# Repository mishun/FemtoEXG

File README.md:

FemtoEXG
========

A simple small-sized DIY bioamplifier + ADC module that can be used
(hopefully) for EEG, ECG or EMG. Made in Eagle CAD.

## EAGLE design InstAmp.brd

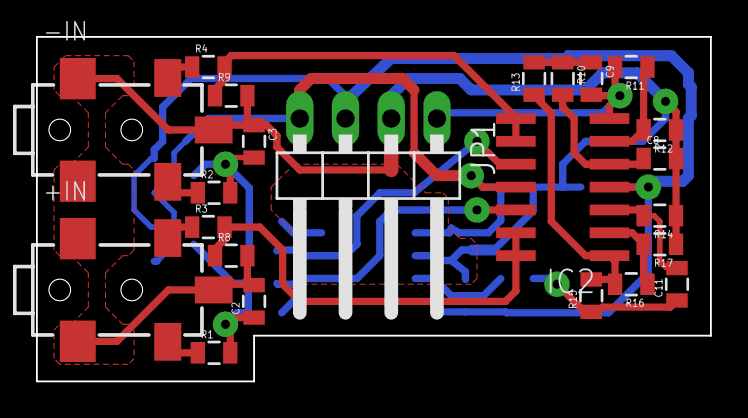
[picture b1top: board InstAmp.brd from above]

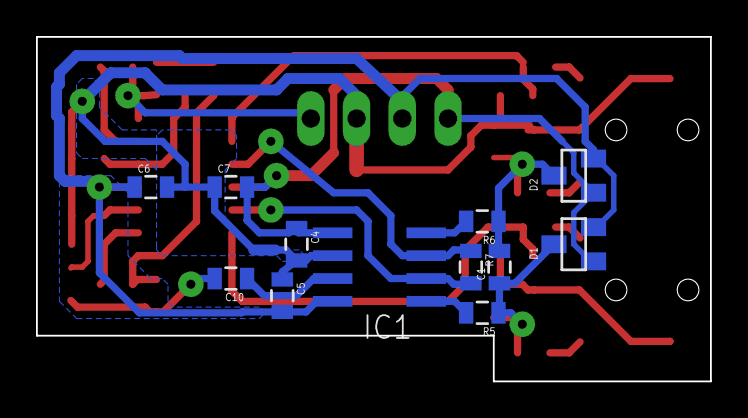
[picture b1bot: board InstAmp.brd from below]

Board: 2 copper layers, 37.4 x 19.1 mm, 35 parts (12 on the bottom side), 24 nets.

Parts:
+IN: AUDIOJACK2.5-SMD
-IN: AUDIOJACK2.5-SMD
C1: 10pF; 0805
C2, C3: 100pF; 0805
C4, C5, C6, C7: 100nF; 0805
C8: 47nF; 0805
C9: 33nF; 0805
C10, C11: 1uF; 0805
D1, D2: BAV199; SOT23
IC1: AD8221ARZ
IC2: TLC2254ID; SO14
JP1: OUT; 1X04/90
R1, R2, R5, R6: 2k2; 0805
R3, R4: 100; 0805
R7: 2k; 0805
R8, R9, R10, R11, R12, R13, R14, R17: 100k; 0805
R15: 680k; 0805
R16: 910k; 0805

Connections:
+5V: C5.2, C6.1, D1.2, D2.2, IC1.8, IC2.4, JP1.3
-5V: C4.1, C7.2, D1.1, D2.1, IC1.5, IC2.11, JP1.4
GND: +IN.GND1, +IN.GND2, +IN.SW, -IN.GND1, -IN.GND2, -IN.SW, C2.2, C3.1, C4.2, C5.1, C6.2, C7.1, C8.2, IC1.6, JP1.2, R8.2, R9.2, R12.1, R14.1, R17.1
unnamed: +IN.L, R1.1
unnamed: -IN.R, R4.1
unnamed: +IN.R, R3.1
unnamed: -IN.L, R2.1
unnamed: C1.2, C3.2, D2.3, R2.2, R6.1
unnamed: C1.1, C2.1, D1.3, R1.2, R5.1
unnamed: IC2.8, IC2.9, R4.2, R9.1
unnamed: IC1.3, IC2.10, R7.1
unnamed: IC2.1, R13.1, R15.2, R16.2
unnamed: IC2.2, R16.1, R17.2
unnamed: C10.1, IC1.7
unnamed: IC1.1, R5.2
unnamed: IC1.4, R6.2
unnamed: C8.1, IC2.5, R10.2
unnamed: C9.1, R10.1, R13.2
unnamed: IC1.2, IC2.12, R7.2
unnamed: IC2.13, IC2.14, R3.2, R8.1
unnamed: C10.2, C11.1, R15.1
unnamed: C11.2, IC2.3, R14.2
unnamed: IC2.6, R11.1, R12.2
OUT: C9.2, IC2.7, JP1.1, R11.2

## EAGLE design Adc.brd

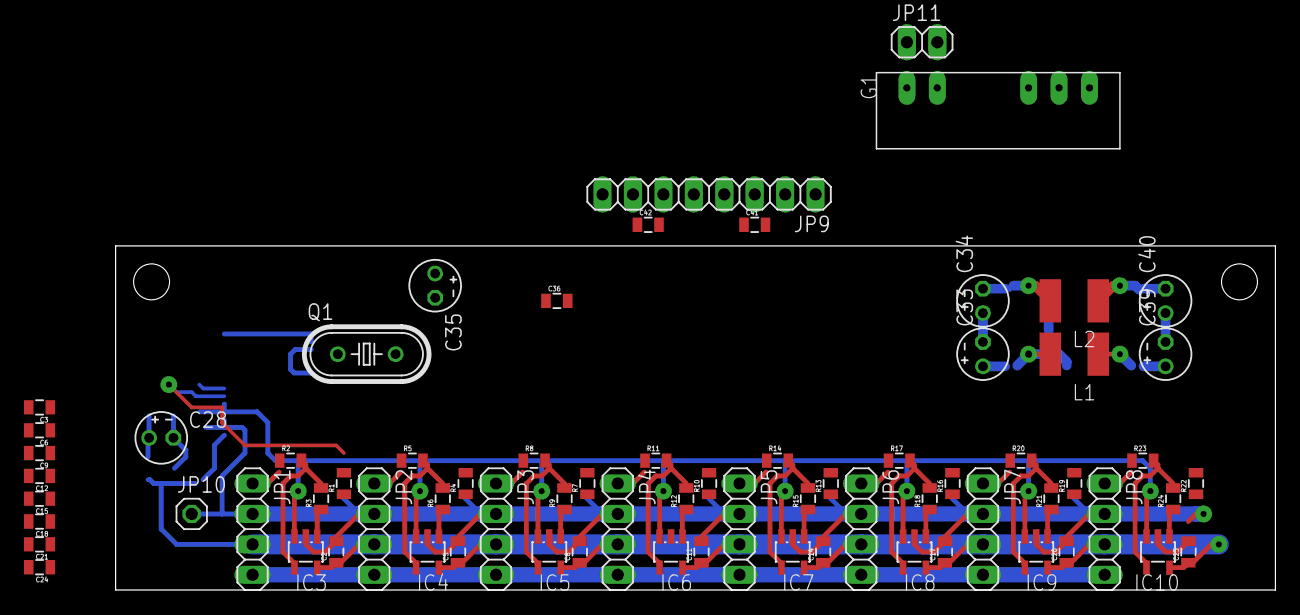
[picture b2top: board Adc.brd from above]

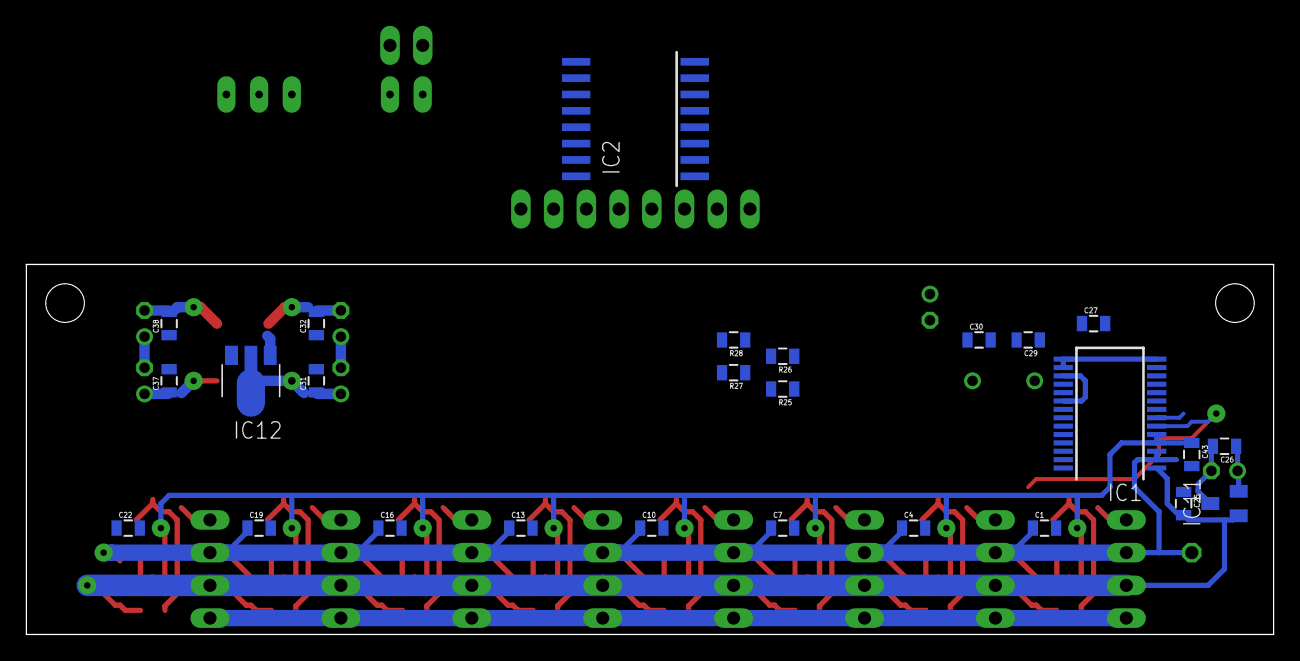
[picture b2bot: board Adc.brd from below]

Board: 2 copper layers, 96.8 x 28.7 mm, 98 parts (26 on the bottom side), 57 nets.

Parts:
C1, C2, C3, C4, C5, C6, C7, C8, C9, C10, C11, C12, C13, C14, C15, C16, C17, C18, C19, C20, C21, C22, C23, C24, C25, C26, C27, C31, C32, C36, C37, C38, C41, C42: 100nF; 0805
C28, C33, C34, C35, C39, C40: 47uF; E2-4
C29, C30: 18pF; 0805
C43: 100pF; 0805
G1: TMV0505D
IC1: ADS1256IDBT
IC2: ADUM1402ARWZ
IC3, IC4, IC5, IC6, IC7, IC8, IC9, IC10: AD8605ARTZ
IC11: REF3125AIDBZT
IC12: MCP170333MB; SOT89
JP1, JP2, JP3, JP4, JP5, JP6, JP7, JP8: 1X04
JP9: 1X08
JP10: 1X01
JP11: 1X02
L1, L2: L4532P
Q1: 7.68MHz; HC49U-V
R1, R4, R7, R10, R13, R16, R19, R22, R25, R26, R27, R28: 100; 0805
R2, R3, R5, R6, R8, R9, R11, R12, R14, R15, R17, R18, R20, R21, R23, R24: 1k; 0805

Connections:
+3.3V: C27.1, C35.+, C36.1, C41.2, IC1.14, IC1.15, IC1.16, IC2.1, IC2.7, IC12.3
+5VA: C2.1, C5.1, C8.1, C11.1, C14.1, C17.1, C20.1, C23.1, C25.2, C37.1, C39.+, IC1.1, IC3.5, IC4.5, IC5.5, IC6.5, IC7.5, IC8.5, IC9.5, IC10.5, IC11.1, JP1.3, JP2.3, JP3.3, JP4.3, JP5.3, JP6.3, JP7.3, JP8.3, L1.1
-5VA: C38.2, C40.-, JP1.4, JP2.4, JP3.4, JP4.4, JP5.4, JP6.4, JP7.4, JP8.4, L2.1
GND: C1.1, C2.2, C3.2, C4.1, C5.2, C6.2, C7.1, C8.2, C9.2, C10.1, C11.2, C12.2, C13.1, C14.2, C15.2, C16.1, C17.2, C18.2, C19.1, C20.2, C21.2, C22.1, C23.2, C24.2, C25.1, C26.2, C27.2, C28.-, C29.2, C30.2, C31.2, C32.1, C33.-, C34.+, C35.-, C36.2, C37.2, C38.1, C39.-, C40.+, C41.1, C43.2, G1.6, IC1.2, IC1.3, IC1.17, IC1.20, IC2.2, IC2.8, IC3.2, IC4.2, IC5.2, IC6.2, IC7.2, IC8.2, IC9.2, IC10.2, IC11.3, IC12.1, JP1.2, JP2.2, JP3.2, JP4.2, JP5.2, JP6.2, JP7.2, JP8.2, JP10.1
unnamed: IC3.4, R2.2, R3.2
unnamed: IC3.1, R1.1, R3.1
unnamed: JP1.1, R2.1
unnamed: C3.1, IC1.6, R1.2
unnamed: IC4.4, R5.2, R6.2
unnamed: IC4.1, R4.1, R6.1
unnamed: C6.1, IC1.7, R4.2
unnamed: JP2.1, R5.1
unnamed: IC5.4, R8.2, R9.2
unnamed: IC5.1, R7.1, R9.1
unnamed: C9.1, IC1.8, R7.2
unnamed: JP3.1, R8.1
unnamed: IC6.4, R11.2, R12.2
unnamed: IC6.1, R10.1, R12.1
unnamed: C12.1, IC1.9, R10.2
unnamed: JP4.1, R11.1
unnamed: IC7.4, R14.2, R15.2
unnamed: IC7.1, R13.1, R15.1
unnamed: C15.1, IC1.10, R13.2
unnamed: JP5.1, R14.1
unnamed: IC8.4, R17.2, R18.2
unnamed: IC8.1, R16.1, R18.1
unnamed: C18.1, IC1.11, R16.2
unnamed: JP6.1, R17.1
unnamed: IC9.4, R20.2, R21.2
unnamed: IC9.1, R19.1, R21.1
unnamed: C21.1, IC1.12, R19.2
unnamed: JP7.1, R20.1
unnamed: IC10.4, R23.2, R24.2
unnamed: IC10.1, R22.1, R24.1
unnamed: C24.1, IC1.13, R22.2
unnamed: JP8.1, R23.1
unnamed: C29.1, IC1.18, Q1.1
unnamed: C30.1, IC1.19, Q1.2
unnamed: IC2.11, JP9.7
unnamed: IC1.21, R25.1
unnamed: IC1.24, R26.1
unnamed: IC1.23, R27.1
unnamed: IC1.22, R28.1
unnamed: C42.1, IC2.9, IC2.15, JP9.8
unnamed: C31.1, C33.+, G1.7, IC12.2@1, L1.2
unnamed: C32.2, C34.-, G1.5, L2.2
unnamed: C42.2, IC2.10, IC2.16, JP9.3
unnamed: IC2.3, R25.2
unnamed: IC2.4, R28.2
unnamed: IC2.5, R26.2
unnamed: IC2.6, R27.2
unnamed: IC2.12, JP9.6
unnamed: IC2.13, JP9.5
unnamed: IC2.14, JP9.4
unnamed: G1.1, JP11.1
unnamed: G1.2, JP11.2
REF: C1.2, C4.2, C7.2, C10.2, C13.2, C16.2, C19.2, C22.2, C26.1, C28.+, C43.1, IC1.4, IC1.5, IC3.3, IC4.3, IC5.3, IC6.3, IC7.3, IC8.3, IC9.3, IC10.3, IC11.2

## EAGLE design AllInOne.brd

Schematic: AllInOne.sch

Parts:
C1, C30, C45, C61, C75, C89, C103, C117: 10pF; C0805
C2, C3, C31, C32, C46, C47, C62, C63, C76, C77, C90, C91, C104, C105, C118, C119: 100pF; C0805
C4, C5, C6, C7, C8, C11, C15, C16, C17, C18, C19, C24, C25, C26, C28, C33, C34, C35, C36, C39, C40, C43, C44, C48, C49, C50, C51, C52, C55, C57, C60, C64, C65, C66, C67, C70, C71, C74, C78, C79, C80, C81, C84, C85, C88, C92, C93, C94, C95, C98, C99, C102, C106, C107, C108, C109, C112, C113, C116, C120, C121, C122, C123, C126, C127, C130: 0.1; C0805
C9, C10: 18p; C0805
C12, C13, C37, C38, C53, C54, C68, C69, C82, C83, C96, C97, C110, C111, C124, C125: 1u; C0805
C14, C41, C58, C72, C86, C100, C114, C128: 47n; C0805
C20, C21, C22, C23, C27, C29: 47u; E2-4
C42, C56, C59, C73, C87, C101, C115, C129: 33n; C0805
COM: COM; 1X02
D1, D2, D3, D4, D5, D6, D7, D8, D9, D10, D11, D12, D13, D14, D15, D16, D17, D18, D19, D20, D21, D22, D23, D24, D25, D26, D27, D28, D29, D30, D31, D32: BAV199; SOT23
G1: TMV0505D
IC1, IC8, IC11, IC14, IC17, IC20, IC23, IC26: AD8221ARZ; SO-08
IC2, IC9, IC12, IC15, IC18, IC21, IC24, IC27: TLC2254ID
IC3: ADS1256IDBT
IC4, IC10, IC13, IC16, IC19, IC22, IC25, IC28: AD8605ARTZ
IC5: MCP170333MB; SOT89
IC6: ADUM1402ARWZ
IC7: REF3125AIDBZT
IN1: IN1; 1X04
IN2: IN2; 1X04
IN3: IN3; 1X04
IN4: IN4; 1X04
IN5: IN5; 1X04
IN6: IN6; 1X04
IN7: IN7; 1X04
IN8: IN8; 1X04
INT: INT; 1X08
L1, L2: 100uH; L4532P
Q1: 8MHz; HC49U-V
R1, R2, R5, R6, R24, R26, R29, R30, R45, R46, R49, R50, R65, R66, R69, R70, R85, R86, R89, R90, R105, R106, R109, R110, R125, R126, R129, R130, R145, R146, R149, R150: 2K2; R0805
R3, R4, R14, R15, R16, R17, R18, R27, R28, R44, R47, R48, R64, R67, R68, R84, R87, R88, R104, R107, R108, R124, R127, R128, R144, R147, R148, R164: 100; R0805
R7, R31, R51, R71, R91, R111, R131, R151: 2K; R0805
R8, R9, R10, R13, R19, R20, R21, R23, R32, R33, R34, R37, R38, R41, R42, R43, R52, R53, R54, R57, R58, R61, R62, R63, R72, R73, R74, R77, R78, R81, R82, R83, R92, R93, R94, R97, R98, R101, R102, R103, R112, R113, R114, R117, R118, R121, R122, R123, R132, R133, R134, R137, R138, R141, R142, R143, R152, R153, R154, R157, R158, R161, R162, R163: 100K; R0805
R11, R35, R55, R75, R95, R115, R135, R155: 910K; R0805
R12, R36, R56, R76, R96, R116, R136, R156: 680K; R0805
R22, R25, R39, R40, R59, R60, R79, R80, R99, R100, R119, R120, R139, R140, R159, R160: 1K; R0805

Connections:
+3.3V: C7.1, C17.1, C21.+, C44.1, IC3.14 (SYNC/PDWN), IC3.15 (RESET), IC3.16 (DVDD), IC5.3 (VO), IC6.1 (VDD1), IC6.7 (VE1)
+5VA: C5.2, C6.1, C8.1, C15.1, C26.1, C27.+, C34.2, C35.1, C39.1, C49.2, C50.1, C55.1, C65.2, C66.1, C70.1, C79.2, C80.1, C84.1, C93.2, C94.1, C98.1, C107.2, C108.1, C112.1, C121.2, C122.1, C126.1, D1.2 (C), D2.2 (C), D3.2 (C), D4.2 (C), D5.2 (C), D6.2 (C), D7.2 (C), D8.2 (C), D9.2 (C), D10.2 (C), D11.2 (C), D12.2 (C), D13.2 (C), D14.2 (C), D15.2 (C), D16.2 (C), D17.2 (C), D18.2 (C), D19.2 (C), D20.2 (C), D21.2 (C), D22.2 (C), D23.2 (C), D24.2 (C), D25.2 (C), D26.2 (C), D27.2 (C), D28.2 (C), D29.2 (C), D30.2 (C), D31.2 (C), D32.2 (C), IC1.8 (+VS), IC2.4 (+VS), IC3.1 (AVDD), IC4.5 (+VS), IC7.1 (VIN), IC8.8 (+VS), IC9.4 (+VS), IC10.5 (+VS), IC11.8 (+VS), IC12.4 (+VS), IC13.5 (+VS), IC14.8 (+VS), IC15.4 (+VS), IC16.5 (+VS), IC17.8 (+VS), IC18.4 (+VS), IC19.5 (+VS), IC20.8 (+VS), IC21.4 (+VS), IC22.5 (+VS), IC23.8 (+VS), IC24.4 (+VS), IC25.5 (+VS), IC26.8 (+VS), IC27.4 (+VS), IC28.5 (+VS), L1.1
-5VA: C4.1, C11.2, C28.2, C29.-, C33.1, C36.2, C48.1, C51.2, C64.1, C67.2, C78.1, C81.2, C92.1, C95.2, C106.1, C109.2, C120.1, C123.2, D1.1 (A), D2.1 (A), D3.1 (A), D4.1 (A), D5.1 (A), D6.1 (A), D7.1 (A), D8.1 (A), D9.1 (A), D10.1 (A), D11.1 (A), D12.1 (A), D13.1 (A), D14.1 (A), D15.1 (A), D16.1 (A), D17.1 (A), D18.1 (A), D19.1 (A), D20.1 (A), D21.1 (A), D22.1 (A), D23.1 (A), D24.1 (A), D25.1 (A), D26.1 (A), D27.1 (A), D28.1 (A), D29.1 (A), D30.1 (A), D31.1 (A), D32.1 (A), IC1.5 (-VS), IC2.11 (-VS), IC8.5 (-VS), IC9.11 (-VS), IC11.5 (-VS), IC12.11 (-VS), IC14.5 (-VS), IC15.11 (-VS), IC17.5 (-VS), IC18.11 (-VS), IC20.5 (-VS), IC21.11 (-VS), IC23.5 (-VS), IC24.11 (-VS), IC26.5 (-VS), IC27.11 (-VS), L2.1
CH1SW1: IC2.7 (OUT2), R11.1, R12.2, R20.2
CH1SW2: IC9.7 (OUT2), R35.1, R36.2, R38.2
CH1SW3: IC12.7 (OUT2), R55.1, R56.2, R58.2
CH1SW4: IC15.7 (OUT2), R75.1, R76.2, R78.2
CH1SW5: IC18.7 (OUT2), R95.1, R96.2, R98.2
CH1SW6: IC21.7 (OUT2), R115.1, R116.2, R118.2
CH1SW7: IC24.7 (OUT2), R135.1, R136.2, R138.2
CH1SW8: IC27.7 (OUT2), R155.1, R156.2, R158.2
GND: C2.2, C3.1, C4.2, C5.1, C6.2, C7.2, C8.2, C9.2, C10.2, C11.1, C14.2, C15.2, C16.2, C17.2, C19.1, C20.-, C21.-, C22.-, C23.+, C24.2, C25.1, C26.2, C27.-, C28.1, C29.+, C31.2, C32.1, C33.2, C34.1, C35.2, C36.1, C39.2, C40.1, C41.2, C43.1, C44.2, C46.2, C47.1, C48.2, C49.1, C50.2, C51.1, C52.1, C55.2, C57.1, C58.2, C60.1, C62.2, C63.1, C64.2, C65.1, C66.2, C67.1, C70.2, C71.1, C72.2, C74.1, C76.2, C77.1, C78.2, C79.1, C80.2, C81.1, C84.2, C85.1, C86.2, C88.1, C90.2, C91.1, C92.2, C93.1, C94.2, C95.1, C98.2, C99.1, C100.2, C102.1, C104.2, C105.1, C106.2, C107.1, C108.2, C109.1, C112.2, C113.1, C114.2, C116.1, C118.2, C119.1, C120.2, C121.1, C122.2, C123.1, C126.2, C127.1, C128.2, C130.1, COM.1, COM.2, G1.6 (COM), IC1.6 (REF), IC3.2 (AGND), IC3.3 (VREFN), IC3.17 (DGND), IC3.20 (CS), IC4.2 (-VS), IC5.1 (GND), IC6.2 (GND1), IC6.8 (GND1_), IC7.3 (GND), IC8.6 (REF), IC10.2 (-VS), IC11.6 (REF), IC13.2 (-VS), IC14.6 (REF), IC16.2 (-VS), IC17.6 (REF), IC19.2 (-VS), IC20.6 (REF), IC22.2 (-VS), IC23.6 (REF), IC25.2 (-VS), IC26.6 (REF), IC28.2 (-VS), R8.2, R9.2, R10.1, R13.2, R21.2, R32.2, R33.2, R34.1, R37.2, R42.2, R52.2, R53.2, R54.1, R57.2, R62.2, R72.2, R73.2, R74.1, R77.2, R82.2, R92.2, R93.2, R94.1, R97.2, R102.2, R112.2, R113.2, R114.1, R117.2, R122.2, R132.2, R133.2, R134.1, R137.2, R142.2, R152.2, R153.2, R154.1, R157.2, R162.2
unnamed: IN1.3, R3.1
unnamed: IN1.2, R4.1
unnamed: IN1.4, R1.1
unnamed: IN1.1, R2.1
unnamed: IC1.1 (-IN), R5.2
unnamed: IC1.4 (+IN), R6.2
unnamed: C1.1, C2.1, D1.3 (AC), R1.2, R5.1
unnamed: C1.2, C3.2, D2.3 (AC), R2.2, R6.1
unnamed: IC1.2 (-RG), IC2.10 (+IN3), R7.2
unnamed: IC1.3 (+RG), IC2.12 (+IN4), R7.1
unnamed: IC3.21 (DRDY), R14.1
unnamed: C10.1, IC3.18 (XTAL2), Q1.1
unnamed: C9.1, IC3.19 (XTAL1/CLKIN), Q1.2
unnamed: IC3.24 (SCLK), R15.1
unnamed: C13.2, IC2.5 (+IN2), R13.1
unnamed: IC2.6 (-IN2), R10.2, R11.2
unnamed: C12.2, C13.1, R12.1
unnamed: C12.1, IC1.7 (OUT)
unnamed: IC2.2 (-IN1), R21.1, R23.1
unnamed: C14.1, IC2.3 (+IN1), R19.1
unnamed: IC4.1 (OUT), R18.2, R25.2
unnamed: IC3.23 (DIN), R16.1
unnamed: IC3.22 (DOUT), R17.1
unnamed: D4.3 (AC), IC2.13 (-IN4), IC2.14 (OUT4), R4.2, R9.1
unnamed: D3.3 (AC), IC2.8 (OUT3), IC2.9 (-IN3), R3.2, R8.1
unnamed: C19.2, IC3.6 (AIN0), R18.1
unnamed: C56.1, R19.2, R20.1
unnamed: IC4.4 (-IN), R22.1, R25.1
unnamed: IN2.3, R27.1
unnamed: IC6.3 (VIA), R14.2
unnamed: IC6.4 (VIB), R17.2
unnamed: IC6.5 (VOC), R15.2
unnamed: IC6.6 (VOD), R16.2
unnamed: G1.1 (+VIN), INT.1
unnamed: C18.2, IC6.9 (GND2_), IC6.15 (GND2), INT.8
unnamed: C18.1, IC6.10 (VE2), IC6.16 (VDD2), INT.3
unnamed: C22.+, C24.1, G1.7 (+VOUT), IC5.2@1 (VI1), L1.2
unnamed: IC6.11 (VID), INT.7
unnamed: IC6.12 (VIC), INT.6
unnamed: IC6.13 (VOB), INT.5
unnamed: IC6.14 (VOA), INT.4
unnamed: C23.-, C25.2, G1.5 (-VOUT), L2.2
unnamed: IN2.2, R28.1
unnamed: IN2.4, R24.1
unnamed: IN2.1, R26.1
unnamed: IC8.1 (-IN), R29.2
unnamed: C30.1, C31.1, D5.3 (AC), R24.2, R29.1
unnamed: C30.2, C32.2, D6.3 (AC), R26.2, R30.1
unnamed: IC8.2 (-RG), IC9.10 (+IN3), R31.2
unnamed: IC8.3 (+RG), IC9.12 (+IN4), R31.1
unnamed: IC8.4 (+IN), R30.2
unnamed: D8.3 (AC), IC9.13 (-IN4), IC9.14 (OUT4), R28.2, R33.1
unnamed: D7.3 (AC), IC9.8 (OUT3), IC9.9 (-IN3), R27.2, R32.1
unnamed: C38.2, IC9.5 (+IN2), R37.1
unnamed: IC9.6 (-IN2), R34.2, R35.2
unnamed: C37.2, C38.1, R36.1
unnamed: C37.1, IC8.7 (OUT)
unnamed: C41.1, IC9.3 (+IN1), R41.1
unnamed: IC10.4 (-IN), R39.1, R40.1
unnamed: IC10.1 (OUT), R40.2, R44.2
unnamed: C56.2, IC2.1 (OUT1), R22.2, R23.2
unnamed: IC9.2 (-IN1), R42.1, R43.1
unnamed: C42.1, R38.1, R41.2
unnamed: C42.2, IC9.1 (OUT1), R39.2, R43.2
unnamed: C43.2, IC3.7 (AIN1), R44.1
unnamed: IN3.3, R47.1
unnamed: IN3.2, R48.1
unnamed: IN3.4, R45.1
unnamed: IN3.1, R46.1
unnamed: IC11.1 (-IN), R49.2
unnamed: C45.1, C46.1, D9.3 (AC), R45.2, R49.1
unnamed: C45.2, C47.2, D10.3 (AC), R46.2, R50.1
unnamed: IC11.2 (-RG), IC12.10 (+IN3), R51.2
unnamed: IC11.3 (+RG), IC12.12 (+IN4), R51.1
unnamed: IC11.4 (+IN), R50.2
unnamed: D12.3 (AC), IC12.13 (-IN4), IC12.14 (OUT4), R48.2, R53.1
unnamed: D11.3 (AC), IC12.8 (OUT3), IC12.9 (-IN3), R47.2, R52.1
unnamed: C54.2, IC12.5 (+IN2), R57.1
unnamed: IC12.6 (-IN2), R54.2, R55.2
unnamed: C53.2, C54.1, R56.1
unnamed: C53.1, IC11.7 (OUT)
unnamed: C58.1, IC12.3 (+IN1), R61.1
unnamed: IC13.4 (-IN), R59.1, R60.1
unnamed: IC13.1 (OUT), R60.2, R64.2
unnamed: IC12.2 (-IN1), R62.1, R63.1
unnamed: C59.1, R58.1, R61.2
unnamed: C59.2, IC12.1 (OUT1), R59.2, R63.2
unnamed: C60.2, IC3.8 (AIN2), R64.1
unnamed: C116.2, IC3.12 (AIN6), R144.1
unnamed: IN5.3, R87.1
unnamed: IN4.3, R67.1
unnamed: IN4.2, R68.1
unnamed: IN4.4, R65.1
unnamed: IN4.1, R66.1
unnamed: IC14.1 (-IN), R69.2
unnamed: C61.1, C62.1, D13.3 (AC), R65.2, R69.1
unnamed: C61.2, C63.2, D14.3 (AC), R66.2, R70.1
unnamed: IC14.2 (-RG), IC15.10 (+IN3), R71.2
unnamed: IC14.3 (+RG), IC15.12 (+IN4), R71.1
unnamed: IC14.4 (+IN), R70.2
unnamed: D16.3 (AC), IC15.13 (-IN4), IC15.14 (OUT4), R68.2, R73.1
unnamed: D15.3 (AC), IC15.8 (OUT3), IC15.9 (-IN3), R67.2, R72.1
unnamed: C69.2, IC15.5 (+IN2), R77.1
unnamed: IC15.6 (-IN2), R74.2, R75.2
unnamed: C68.2, C69.1, R76.1
unnamed: C68.1, IC14.7 (OUT)
unnamed: C72.1, IC15.3 (+IN1), R81.1
unnamed: IC16.4 (-IN), R79.1, R80.1
unnamed: IC16.1 (OUT), R80.2, R84.2
unnamed: IC15.2 (-IN1), R82.1, R83.1
unnamed: C73.1, R78.1, R81.2
unnamed: C73.2, IC15.1 (OUT1), R79.2, R83.2
unnamed: C74.2, IC3.9 (AIN3), R84.1
unnamed: IN5.2, R88.1
unnamed: IN5.4, R85.1
unnamed: IN5.1, R86.1
unnamed: IC17.1 (-IN), R89.2
unnamed: C75.1, C76.1, D17.3 (AC), R85.2, R89.1
unnamed: C75.2, C77.2, D18.3 (AC), R86.2, R90.1
unnamed: IC17.2 (-RG), IC18.10 (+IN3), R91.2
unnamed: IC17.3 (+RG), IC18.12 (+IN4), R91.1
unnamed: IC17.4 (+IN), R90.2
unnamed: D20.3 (AC), IC18.13 (-IN4), IC18.14 (OUT4), R88.2, R93.1
unnamed: D19.3 (AC), IC18.8 (OUT3), IC18.9 (-IN3), R87.2, R92.1
unnamed: C83.2, IC18.5 (+IN2), R97.1
unnamed: IC18.6 (-IN2), R94.2, R95.2
unnamed: C82.2, C83.1, R96.1
unnamed: C82.1, IC17.7 (OUT)
unnamed: C86.1, IC18.3 (+IN1), R101.1
unnamed: IC19.4 (-IN), R99.1, R100.1
unnamed: IC19.1 (OUT), R100.2, R104.2
unnamed: IC18.2 (-IN1), R102.1, R103.1
unnamed: C87.1, R98.1, R101.2
unnamed: C87.2, IC18.1 (OUT1), R99.2, R103.2
unnamed: C88.2, IC3.10 (AIN4), R104.1
unnamed: IN6.3, R107.1
unnamed: IN6.2, R108.1
unnamed: IN6.4, R105.1
unnamed: IN6.1, R106.1
unnamed: IC20.1 (-IN), R109.2
unnamed: C89.1, C90.1, D21.3 (AC), R105.2, R109.1
unnamed: C89.2, C91.2, D22.3 (AC), R106.2, R110.1
unnamed: IC20.2 (-RG), IC21.10 (+IN3), R111.2
unnamed: IC20.3 (+RG), IC21.12 (+IN4), R111.1
unnamed: IC20.4 (+IN), R110.2
unnamed: D24.3 (AC), IC21.13 (-IN4), IC21.14 (OUT4), R108.2, R113.1
unnamed: D23.3 (AC), IC21.8 (OUT3), IC21.9 (-IN3), R107.2, R112.1
unnamed: C97.2, IC21.5 (+IN2), R117.1
unnamed: IC21.6 (-IN2), R114.2, R115.2
unnamed: C96.2, C97.1, R116.1
unnamed: C96.1, IC20.7 (OUT)
unnamed: C100.1, IC21.3 (+IN1), R121.1
unnamed: IC22.4 (-IN), R119.1, R120.1
unnamed: IC22.1 (OUT), R120.2, R124.2
unnamed: IC21.2 (-IN1), R122.1, R123.1
unnamed: C101.1, R118.1, R121.2
unnamed: C101.2, IC21.1 (OUT1), R119.2, R123.2
unnamed: C102.2, IC3.11 (AIN5), R124.1
unnamed: IN7.3, R127.1
unnamed: IN7.2, R128.1
unnamed: IN7.4, R125.1
unnamed: IN7.1, R126.1
unnamed: IC23.1 (-IN), R129.2
unnamed: C103.1, C104.1, D25.3 (AC), R125.2, R129.1
unnamed: C103.2, C105.2, D26.3 (AC), R126.2, R130.1
unnamed: IC23.2 (-RG), IC24.10 (+IN3), R131.2
unnamed: IC23.3 (+RG), IC24.12 (+IN4), R131.1
unnamed: IC23.4 (+IN), R130.2
unnamed: D28.3 (AC), IC24.13 (-IN4), IC24.14 (OUT4), R128.2, R133.1
unnamed: D27.3 (AC), IC24.8 (OUT3), IC24.9 (-IN3), R127.2, R132.1
unnamed: C111.2, IC24.5 (+IN2), R137.1
unnamed: IC24.6 (-IN2), R134.2, R135.2
unnamed: C110.2, C111.1, R136.1
unnamed: C110.1, IC23.7 (OUT)
unnamed: C114.1, IC24.3 (+IN1), R141.1
unnamed: IC25.4 (-IN), R139.1, R140.1
unnamed: IC25.1 (OUT), R140.2, R144.2
unnamed: IC24.2 (-IN1), R142.1, R143.1
unnamed: C115.1, R138.1, R141.2
unnamed: C115.2, IC24.1 (OUT1), R139.2, R143.2
unnamed: C130.2, IC3.13 (AIN7), R164.1
unnamed: IN8.3, R147.1
unnamed: IN8.2, R148.1
unnamed: IN8.4, R145.1
unnamed: IN8.1, R146.1
unnamed: IC26.1 (-IN), R149.2
unnamed: C117.1, C118.1, D29.3 (AC), R145.2, R149.1
unnamed: C117.2, C119.2, D30.3 (AC), R146.2, R150.1
unnamed: IC26.2 (-RG), IC27.10 (+IN3), R151.2
unnamed: IC26.3 (+RG), IC27.12 (+IN4), R151.1
unnamed: IC26.4 (+IN), R150.2
unnamed: D32.3 (AC), IC27.13 (-IN4), IC27.14 (OUT4), R148.2, R153.1
unnamed: D31.3 (AC), IC27.8 (OUT3), IC27.9 (-IN3), R147.2, R152.1
unnamed: C125.2, IC27.5 (+IN2), R157.1
unnamed: IC27.6 (-IN2), R154.2, R155.2
unnamed: C124.2, C125.1, R156.1
unnamed: C124.1, IC26.7 (OUT)
unnamed: C128.1, IC27.3 (+IN1), R161.1
unnamed: IC28.4 (-IN), R159.1, R160.1
unnamed: IC28.1 (OUT), R160.2, R164.2
unnamed: IC27.2 (-IN1), R162.1, R163.1
unnamed: C129.1, R158.1, R161.2
unnamed: C129.2, IC27.1 (OUT1), R159.2, R163.2
unnamed: G1.2 (-VIN), INT.2
VREF: C16.1, C20.+, C40.2, C52.2, C57.2, C71.2, C85.2, C99.2, C113.2, C127.2, IC3.4 (VREFP), IC3.5 (AINCOM), IC4.3 (+IN), IC7.2 (VOUT), IC10.3 (+IN), IC13.3 (+IN), IC16.3 (+IN), IC19.3 (+IN), IC22.3 (+IN), IC25.3 (+IN), IC28.3 (+IN)

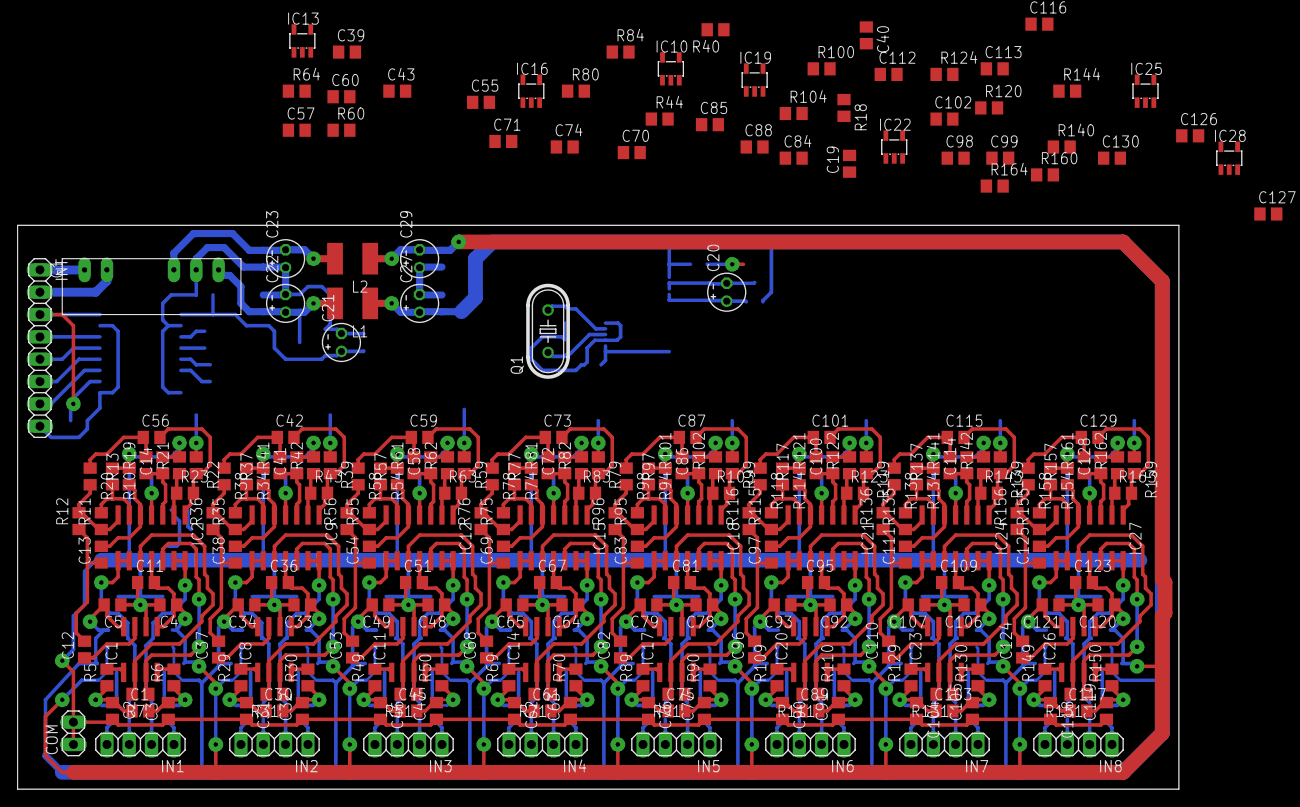
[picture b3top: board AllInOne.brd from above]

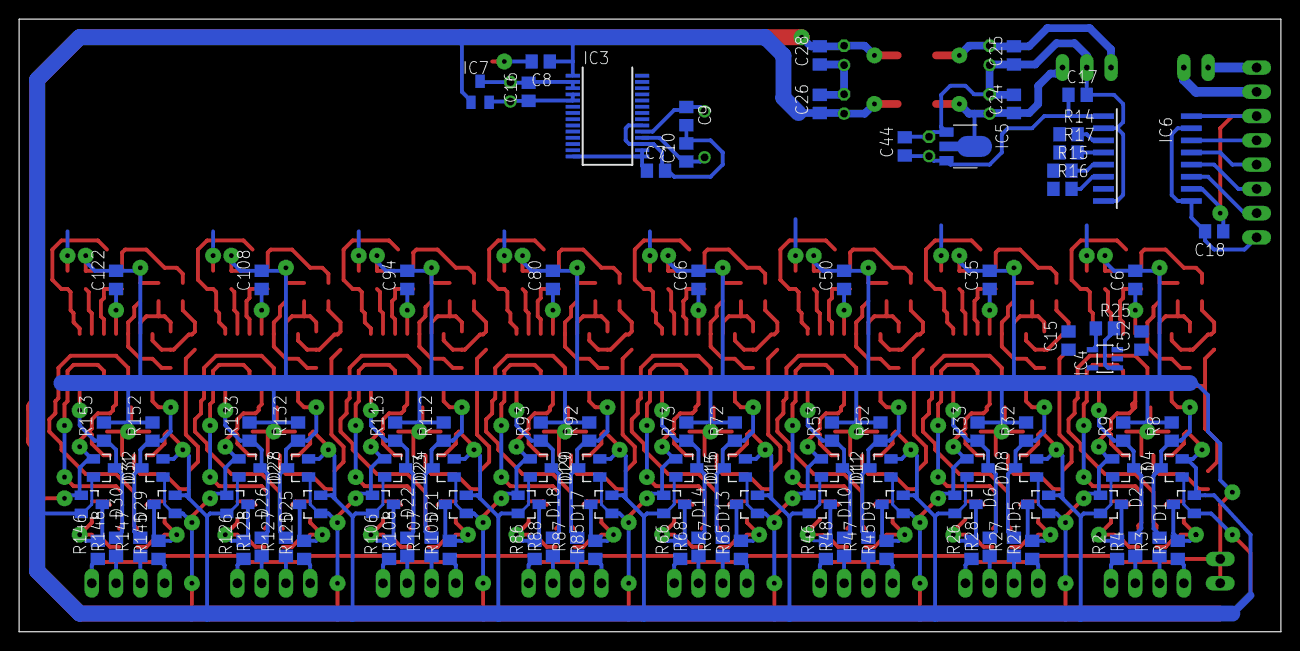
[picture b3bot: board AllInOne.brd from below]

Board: 2 copper layers, 132.1 x 64.1 mm, 368 parts (112 on the bottom side), 217 nets.

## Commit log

2013-03-26 Existing files added
2013-04-03 Circuit alpha version; routing in progress
2013-04-16 Filters are routed
2013-04-17 Some power lines routed
2013-07-10 Latest modification for all-in-one board
2013-07-10 Separate instrumentation amplifier board added
2013-07-10 All-in-one board renamed
2013-07-10 More specific .gitignore
2013-07-10 Separate ADC board added
2013-07-12 Rename lbr
2013-07-30 Dimensions
2013-08-01 Routing
2013-08-01 Simplification of circuit
2013-08-02 Readme update
2013-08-08 Amp routing
2013-08-17 Better comps
2013-08-28 Dimension correction
2013-11-20 Polygons

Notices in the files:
parts and their libraries:
SparkFun-Passives: Licensing: CC v3.0 Share-Alike You are welcome to use this library for commercial purposes.
